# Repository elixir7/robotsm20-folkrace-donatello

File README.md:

# Donatello Folkrace robot
He look.

He think.

But most importantly

He hack.

# PCB
The robot has 3 different circuitboards:
- 5x Laser sensor boards 
- 1x MCU board
- 1x Motor board
The sensors connects to the MCU board and the MCU board to the motor board.

## Laser sensor board

A tiny pcb with a laser distance sensor (VL53L1X) creating a 2D lidar by fusion data from multiple sensors.
The sensor has a programmable reciever meaning it is possible to get more distance readings from different angles.

The 5 boards create a 135 deg field of view , ~6.5 deg resolution and  20 data points.

## MCU board

It's the brain of the robot and contains a STM32F031G6 Arm Cortex M0 microcontroller. It also has connectors for all sensors, LED, servo feedback connector and voltage regulator.

## Motor board

Contains 2 DC motor drivers (MAX14780) and connector the for battery.

# 3D Scan
Point cloud data of the base car, a Kyosho Mini Z Inferno Buggy.

 Post processed 3D Scan with textures.

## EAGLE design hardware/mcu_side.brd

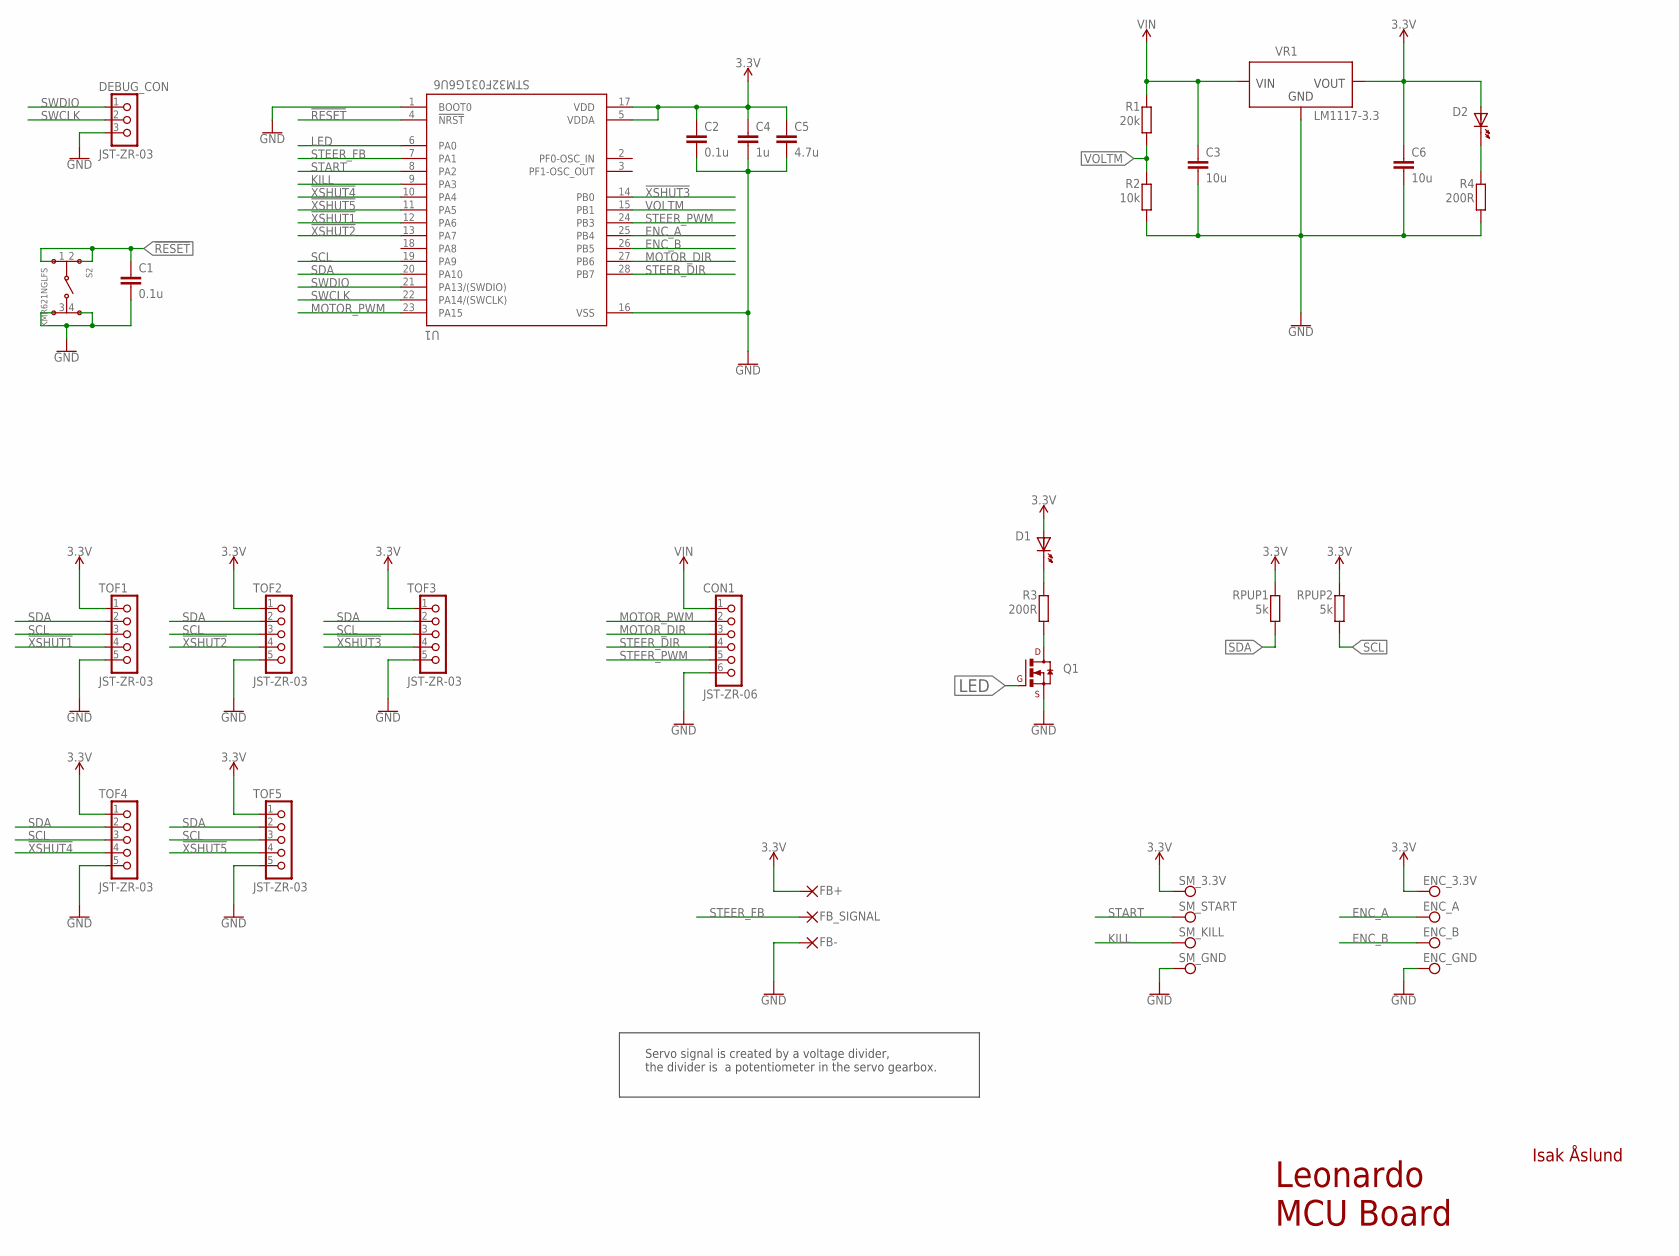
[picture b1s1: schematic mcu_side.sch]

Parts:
C1, C2: 0.1u; C0603
C3, C6: 10u; C1206
C4: 1u; C0603
C5: 4.7u; C0603
CON1: JST-ZR-06; B6B-ZR
D1, D2: CHIP-LED0603
DEBUG_CON: JST-ZR-03; B3B-ZR
ENC_3.3V: PAD-SMD-ROUND-1.27PAD; PAD.03X.05
ENC_A: PAD-SMD-ROUND-1.27PAD; PAD.03X.05
ENC_B: PAD-SMD-ROUND-1.27PAD; PAD.03X.05
ENC_GND: PAD-SMD-ROUND-1.27PAD; PAD.03X.05
FB+: SMD2; SMD1,27-2,54
FB-: SMD2; SMD1,27-2,54
FB_SIGNAL: SMD2; SMD1,27-2,54
Q1: BSS138LT3G; SOT23
R1: 20k; R0603
R2: 10k; R0603
R3, R4: 200R; R0603
RPUP1, RPUP2: 5k; R0603
S2: KMR621NGLFS
SM_3.3V: PAD-SMD-ROUND-1.27PAD; PAD.03X.05
SM_GND: PAD-SMD-ROUND-1.27PAD; PAD.03X.05
SM_KILL: PAD-SMD-ROUND-1.27PAD; PAD.03X.05
SM_START: PAD-SMD-ROUND-1.27PAD; PAD.03X.05
TOF1, TOF2, TOF3, TOF4, TOF5: JST-ZR-03; B5B-ZR
U1: STM32F031G6U6; QFN50P400X400X60-28N
VR1: LM1117-3.3; SOT230P700X180-4

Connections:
3.3V: C2.1, C4.1, C5.1, C6.1, D1.A, D2.A, ENC_3.3V.P$1, FB+.1, RPUP1.1, RPUP2.1, SM_3.3V.P$1, TOF1.1, TOF2.1, TOF3.1, TOF4.1, TOF5.1, U1.5 (VDDA), U1.17 (VDD), VR1.2 (VOUT), VR1.4 (VOUT)
!RESET: C1.1, S2.1, S2.2, U1.4 (!NRST)
!XSHUT1: TOF1.4, U1.12 (PA6)
!XSHUT2: TOF2.4, U1.13 (PA7)
!XSHUT3: TOF3.4, U1.14 (PB0)
!XSHUT4: TOF4.4, U1.10 (PA4)
!XSHUT5: TOF5.4, U1.11 (PA5)
ENC_A: ENC_A.P$1, U1.25 (PB4)
ENC_B: ENC_B.P$1, U1.26 (PB5)
GND: C1.2, C2.2, C3.2, C4.2, C5.2, C6.2, CON1.6, DEBUG_CON.3, ENC_GND.P$1, FB-.1, Q1.2 (S), R2.2, R4.2, S2.3, S2.4, SM_GND.P$1, TOF1.5, TOF2.5, TOF3.5, TOF4.5, TOF5.5, U1.1 (BOOT0), U1.16 (VSS), VR1.1 (GND)
KILL: SM_KILL.P$1, U1.9 (PA3)
LED: Q1.1 (G), U1.6 (PA0)
MOTOR_DIR: CON1.3, U1.27 (PB6)
MOTOR_PWM: CON1.2, U1.23 (PA15)
unnamed: D1.C (K), R3.1
unnamed: D2.C (K), R4.1
unnamed: Q1.3 (D), R3.2
SCL: RPUP2.2, TOF1.3, TOF2.3, TOF3.3, TOF4.3, TOF5.3, U1.19 (PA9)
SDA: RPUP1.2, TOF1.2, TOF2.2, TOF3.2, TOF4.2, TOF5.2, U1.20 (PA10)
START: SM_START.P$1, U1.8 (PA2)
STEER_DIR: CON1.4, U1.28 (PB7)
STEER_FB: FB_SIGNAL.1, U1.7 (PA1)
STEER_PWM: CON1.5, U1.24 (PB3)
SWCLK: DEBUG_CON.2, U1.22 (PA14/(SWCLK))
SWDIO: DEBUG_CON.1, U1.21 (PA13/(SWDIO))
VIN: C3.1, CON1.1, R1.1, VR1.3 (VIN)
VOLTM: R1.2, R2.1, U1.15 (PB1)

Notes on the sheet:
Leonardo MCU Board
Isak Åslund
Servo signal is created by a voltage divider, the divider is a potentiometer in the servo gearbox.

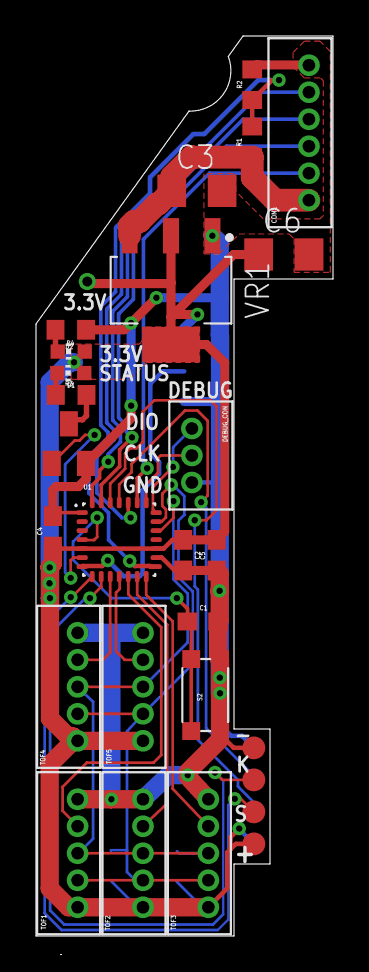
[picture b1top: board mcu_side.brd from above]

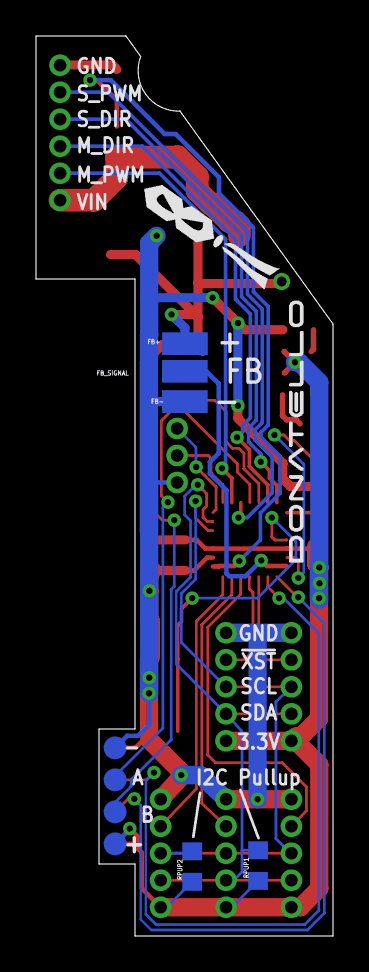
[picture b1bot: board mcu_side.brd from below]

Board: 2 copper layers, 16.5 x 50.0 mm, 36 parts (9 on the bottom side), 27 nets.

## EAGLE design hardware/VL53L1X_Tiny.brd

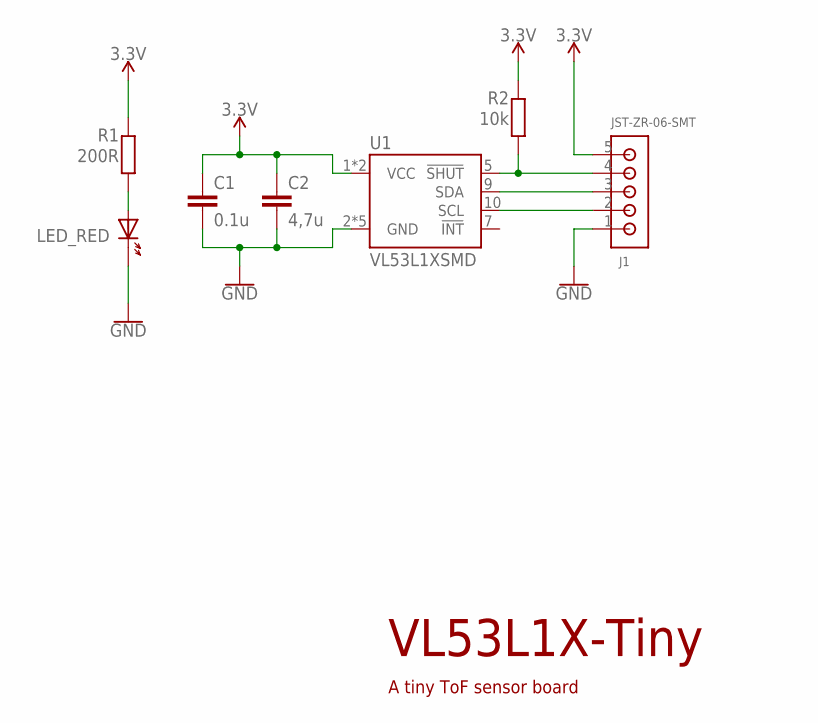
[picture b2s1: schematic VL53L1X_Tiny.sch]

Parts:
C1: 0.1u; C0603
C2: 4,7u; C0603
J1: JST-ZR-06-SMT; JST_B5B-ZR-SM4-TF_LF_SN_0
LED_RED: CHIP-LED0603
R1: 200R; R0603
R2: 10k; R0603
U1: VL53L1XSMD; VL53L1X

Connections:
3.3V: C1.1, C2.1, J1.5, R1.2, R2.2, U1.1 (VCC), U1.11 (VCC)
!SHUT: J1.4, R2.1, U1.5 (!SHUT)
GND: C1.2, C2.2, J1.1, LED_RED.C (K), U1.2 (GND), U1.3 (GND), U1.4 (GND), U1.6 (GND), U1.12 (GND)
unnamed: LED_RED.A, R1.1
SCL: J1.2, U1.10 (SCL)
SDA: J1.3, U1.9 (SDA)

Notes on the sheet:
VL53L1X-Tiny
A tiny ToF sensor board

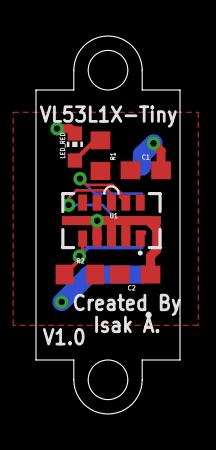
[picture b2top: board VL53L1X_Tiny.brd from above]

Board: 2 copper layers, 8.0 x 21.0 mm, 7 parts (1 on the bottom side), 6 nets.

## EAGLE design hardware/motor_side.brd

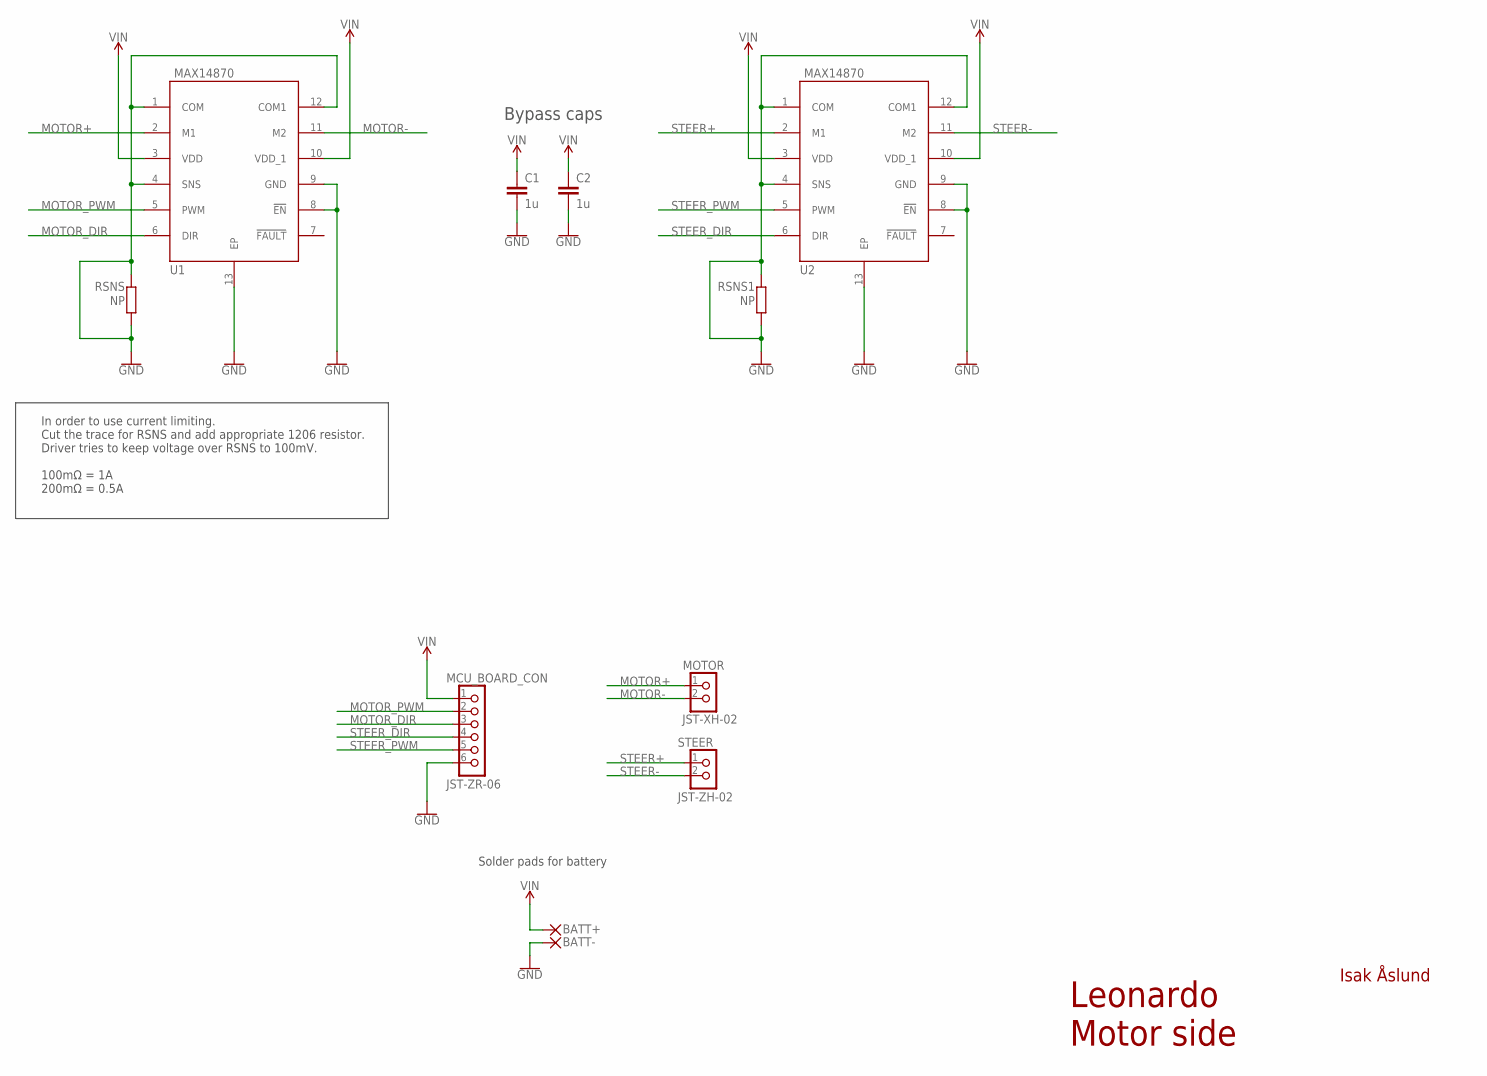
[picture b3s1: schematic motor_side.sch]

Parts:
BATT+: SMD2; SMD1,27-2,54
BATT-: SMD2; SMD1,27-2,54
C1, C2: 1u; C0603
MCU_BOARD_CON: JST-ZR-06; B6B-ZR
MOTOR: JST-XH-02
RSNS, RSNS1: NP; R1206
STEER: JST-ZH-02; B2B-ZR
U1, U2: MAX14870; 12_TDFN_EP

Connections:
GND: BATT-.1, C1.2, C2.2, MCU_BOARD_CON.6, RSNS.1, RSNS.2, RSNS1.1, RSNS1.2, U1.1 (COM), U1.4 (SNS), U1.8 (!EN), U1.9 (GND), U1.12 (COM1), U1.13 (EP), U2.1 (COM), U2.4 (SNS), U2.8 (!EN), U2.9 (GND), U2.12 (COM1), U2.13 (EP)
MOTOR+: MOTOR.1, U1.2 (M1)
MOTOR-: MOTOR.2, U1.11 (M2)
MOTOR_DIR: MCU_BOARD_CON.3, U1.6 (DIR)
MOTOR_PWM: MCU_BOARD_CON.2, U1.5 (PWM)
STEER+: STEER.1, U2.2 (M1)
STEER-: STEER.2, U2.11 (M2)
STEER_DIR: MCU_BOARD_CON.4, U2.6 (DIR)
STEER_PWM: MCU_BOARD_CON.5, U2.5 (PWM)
VIN: BATT+.1, C1.1, C2.1, MCU_BOARD_CON.1, U1.3 (VDD), U1.10 (VDD_1), U2.3 (VDD), U2.10 (VDD_1)

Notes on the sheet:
Leonardo Motor side
Isak Åslund
In order to use current limiting. Cut the trace for RSNS and add appropriate 1206 resistor. Driver tries to keep voltage over RSNS to 100mV. 100mΩ = 1A 200mΩ = 0.5A
Bypass caps
Solder pads for battery

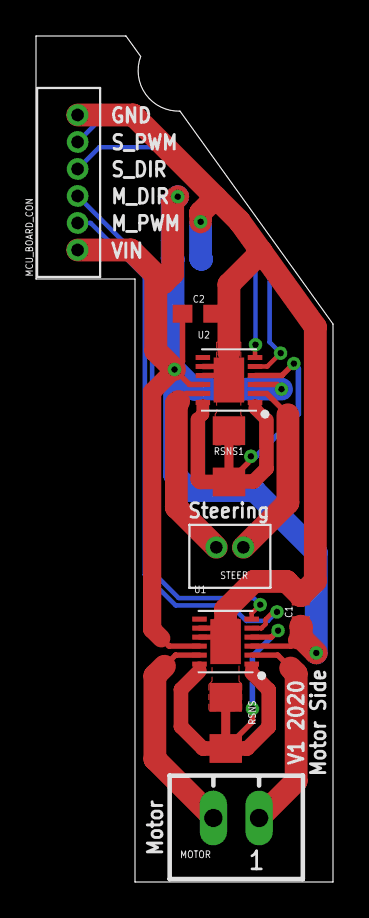
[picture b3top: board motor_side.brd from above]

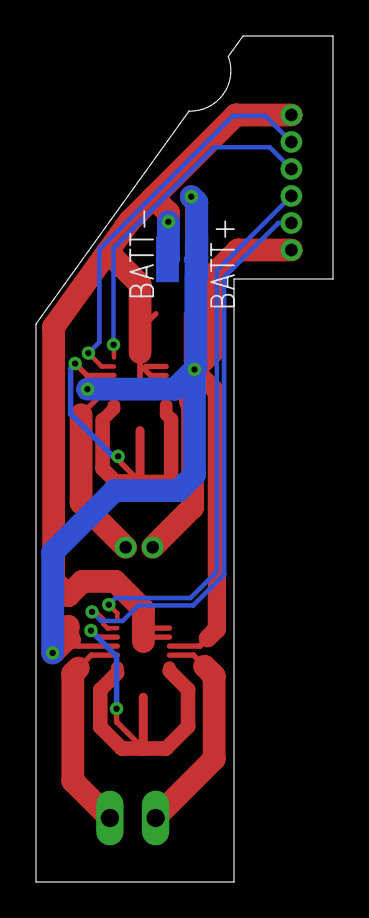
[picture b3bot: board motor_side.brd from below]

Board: 2 copper layers, 16.5 x 47.0 mm, 11 parts (2 on the bottom side), 10 nets.

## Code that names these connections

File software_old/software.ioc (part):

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Mcu.Name=STM32F031G(4-6)Ux
Mcu.Package=UFQFPN28
Mcu.UserName=STM32F031G6Ux
PA0.GPIOParameters=GPIO_Label
PA0.GPIO_Label=LED
PA0.Signal=GPIO_Output
PA1.GPIOParameters=GPIO_Label
PA1.GPIO_Label=STEER_FB
PA1.Mode=IN1
PA1.Signal=ADC_IN1
PA10.GPIOParameters=GPIO_Label
PA10.GPIO_Label=SDA
PA10.Mode=I2C
PA10.Signal=I2C1_SDA
PA13.GPIOParameters=GPIO_Label
PA13.GPIO_Label=SWDIO
PA13.Mode=Serial_Wire
PA13.Signal=SYS_SWDIO
PA14.GPIOParameters=GPIO_Label
PA14.GPIO_Label=SWCLK
PA14.Mode=Serial_Wire
PA14.Signal=SYS_SWCLK
PA15.GPIOParameters=GPIO_Label
PA15.GPIO_Label=MOTOR_PWM
PA15.Signal=S_TIM2_CH1_ETR
PA2.GPIOParameters=GPIO_Label
PA2.GPIO_Label=START
PA2.Signal=GPXTI2
PA3.GPIOParameters=GPIO_Label
PA3.GPIO_Label=KILL
PA3.Signal=GPXTI3
PA4.GPIOParameters=GPIO_Label
PA4.GPIO_Label=XSHUT4
PA4.Signal=GPIO_Output
PA5.GPIOParameters=GPIO_Label
PA5.GPIO_Label=XSHUT5
PA5.Signal=GPIO_Output
PA6.GPIOParameters=GPIO_Label
PA6.GPIO_Label=XSHUT1
PA6.Signal=GPIO_Output
PA7.GPIOParameters=GPIO_Label
PA7.GPIO_Label=XSHUT2
PA7.Signal=GPIO_Output
PA9.GPIOParameters=GPIO_Label
PA9.GPIO_Label=SCL
PA9.Mode=I2C
PA9.Signal=I2C1_SCL
PB0.GPIOParameters=GPIO_Label
PB0.GPIO_Label=XSHUT3
PB0.Signal=GPIO_Output
PB1.GPIOParameters=GPIO_Label
PB1.GPIO_Label=VOLTM
PB1.Mode=IN9
PB1.Signal=ADC_IN9
PB3.GPIOParameters=GPIO_Label
PB3.GPIO_Label=STEER_PWM
PB3.Signal=S_TIM2_CH2
PB4.GPIOParameters=GPIO_Label
PB4.GPIO_Label=ENC_A
PB4.Signal=S_TIM3_CH1
PB5.GPIOParameters=GPIO_Label
PB5.GPIO_Label=ENC_B
PB5.Signal=S_TIM3_CH2
PB6.GPIOParameters=GPIO_Label
PB6.GPIO_Label=MOTOR_DIR
PB6.Signal=GPIO_Output
PB7.GPIOParameters=GPIO_Label
PB7.GPIO_Label=STEER_DIR
PB7.Signal=GPIO_Output
board=custom

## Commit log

2020-03-22 Leonardo V1
2020-03-22 CubeMX pinout init
2020-03-23 Add start module
2020-03-23 Pinconfig for start module
2020-03-24 Logo and name on tPlace/bPlace
2020-03-24 Added todo before production
2020-03-24 Important readme update
2020-03-24 3D Scan and pcb imgs + readme update
2020-03-24 rename of imgs
2020-03-24 test
2020-03-24 test2
2020-03-31 Production ready
2020-04-15 STM32CubeIDE project setup
2020-07-03 Motor working
2020-08-11 VReg changed to linear LM1117, 3.3V
    The switching VREG burned the MCU twice..... Switched to an old classic :)

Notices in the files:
parts and their libraries:
SparkFun-PowerSymbols: Licensing: Creative Commons ShareAlike 4.0 International - https://creativecommons.org/licenses/by-sa/4.0
